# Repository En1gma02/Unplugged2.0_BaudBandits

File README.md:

BaudBandits

- kicad schematic
- kicad pcb
- cad model 
- 3d-cad (Contains screenshots of CAD)
- pcb (Contains screenshots of PCB)

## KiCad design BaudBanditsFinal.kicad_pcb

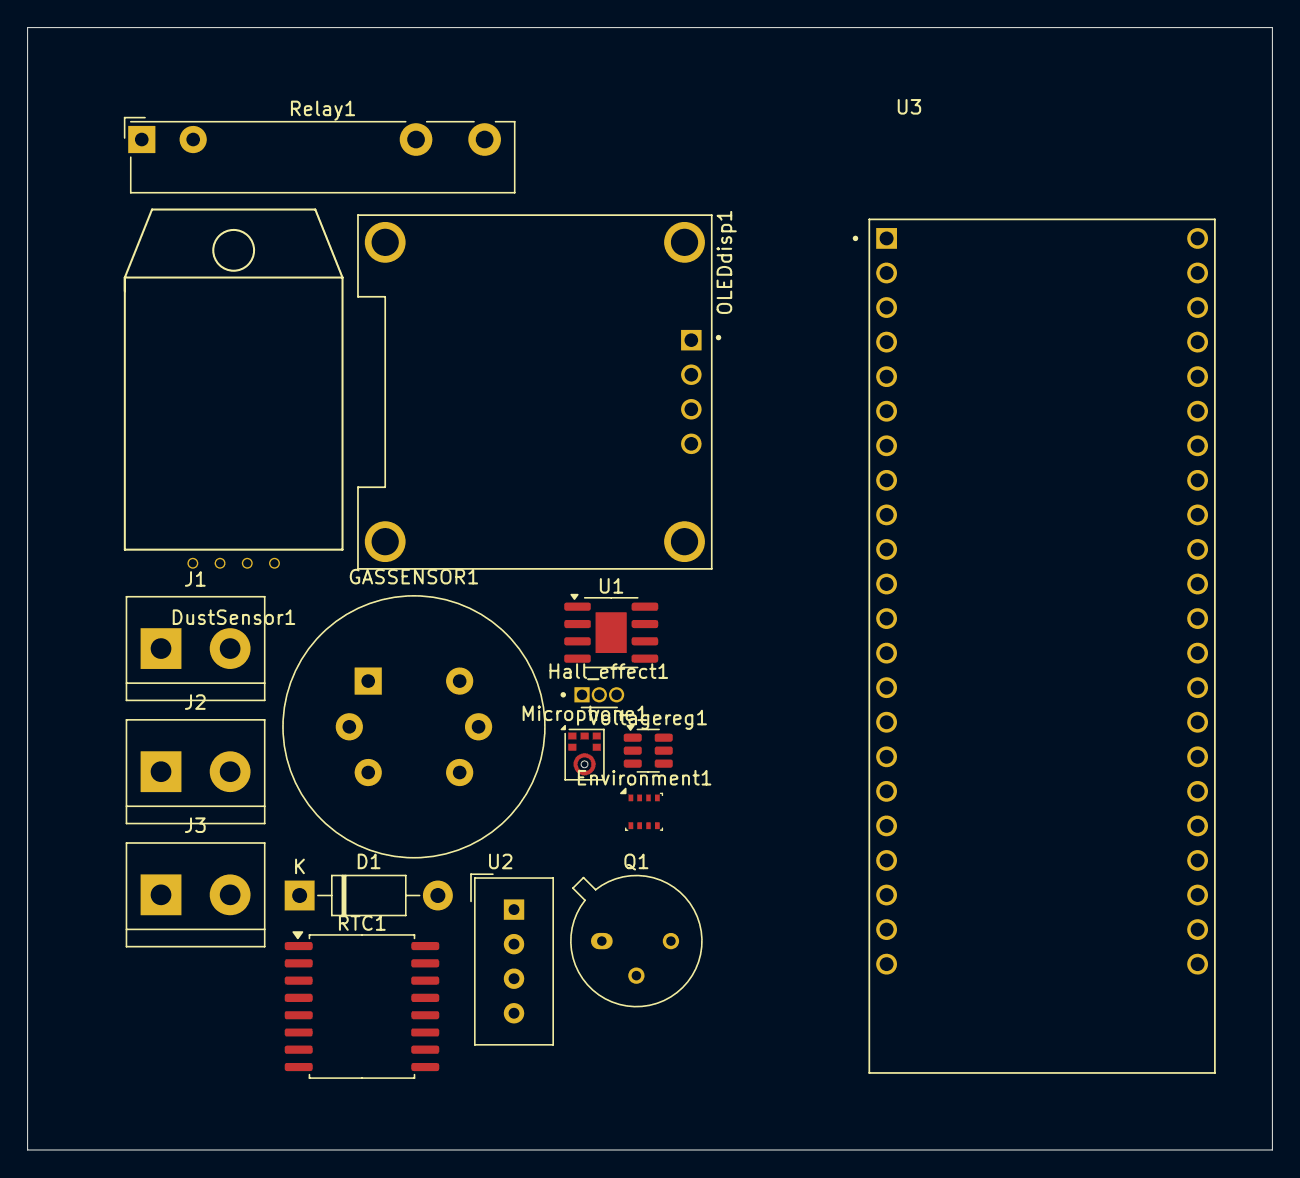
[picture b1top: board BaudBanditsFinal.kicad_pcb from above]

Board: 2 copper layers, 91.5 x 82.5 mm, 17 parts (0 on the bottom side), 19 nets, no tracks yet.

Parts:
D1: 1N5819; D_DO-41_SOD81_P10.16mm_Horizontal
DustSensor1: DHT22
Environment1: BME280; Bosch_LGA-8_2.5x2.5mm_P0.65mm_ClockwisePinNumbering
GASSENSOR1: MQ-6
Hall_effect1: MLX90217LUA-CAA-000-BU; TO92127P410H430-3
J1, J2, J3: Screw_Terminal_01x02; TerminalBlock_bornier-2_P5.08mm
Microphone1: ICS-43434; InvenSense_ICS-43434-6_3.5x2.65mm
OLEDdisp1: DM-OLED096-636; MODULE_DM-OLED096-636
Q1: 2N2219; TO-39-3
RTC1: DS3231M; SOIC-16W_7.5x10.3mm_P1.27mm
Relay1: Fujitsu_FTR-LYAA005x; Relay_SPST-NO_Fujitsu_FTR-LYAA005x_FormA_Vertical
U1: TP4056; SOIC-8-1EP_3.9x4.9mm_P1.27mm_EP2.29x3mm
U2: DHT11; Aosong_DHT11_5.5x12.0_P2.54mm
U3: ESP32-S3-DEVKITC-1-N8R2; XCVR_ESP32-S3-DEVKITC-1-N8R2
Voltagereg1: MT3608; SOT-23-6

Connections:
+5V: GASSENSOR1.2 (VH+), GASSENSOR1.4 (A2), Relay1.A2
/3V3: DustSensor1.1 (VCC), Environment1.2 (CSB), Environment1.8 (VDD), Hall_effect1.1 (VDD), Microphone1.5 (VDD), OLEDdisp1.2 (VCC_IN), RTC1.2 (VCC), U2.1 (VDD), U3.J1_1 (3V3), U3.J1_2 (3V3), Voltagereg1.3 (FB)
/GND: DustSensor1.4 (GND), Environment1.1 (GND), Environment1.5 (SDO), Environment1.7 (GND), GASSENSOR1.3 (B2), GASSENSOR1.5 (VH-), Hall_effect1.2 (GND), Microphone1.3 (GND), OLEDdisp1.1 (GND), Q1.1 (E), RTC1.5 (GND), RTC1.6 (GND), RTC1.7 (GND), RTC1.8 (GND), RTC1.9 (GND), RTC1.10 (GND), RTC1.11 (GND), RTC1.12 (GND), RTC1.13 (GND), U2.4 (GND), U3.J1_22 (GND), U3.J3_1 (GND), U3.J3_21 (GND), U3.J3_22 (GND), Voltagereg1.2 (GND)
/GPIO0: GASSENSOR1.1 (B1), U3.J3_14 (GPIO0)
/GPIO1: DustSensor1.2 (DATA), GASSENSOR1.6 (A1), U3.J3_4 (GPIO1)
/GPIO3: U2.2 (DATA), U3.J1_13 (GPIO3)
/GPIO15: Microphone1.6 (SD), U3.J1_8 (GPIO15)
/GPIO16: Microphone1.4 (SCK), U3.J1_9 (GPIO16)
/GPIO17: Microphone1.1 (WS), Microphone1.2 (LR), U3.J1_10 (GPIO17)
/GPIO18: Environment1.4 (SCK), U3.J1_11 (GPIO18)
/USB_D-/GPIO19: Environment1.3 (SDI), U3.J3_20 (USB_D-/GPIO19)
unnamed: J2.2, U1.3 (GND)
unnamed: D1.2 (A), J1.2
unnamed: D1.1 (K), U1.4 (VCC)
unnamed: J3.2, U1.5 (BAT), Voltagereg1.4 (EN), Voltagereg1.5 (IN)
unnamed: OLEDdisp1.3 (SCL), RTC1.16 (SCL), U3.J1_15 (GPIO9)
unnamed: OLEDdisp1.4 (SDA), RTC1.15 (SDA), U3.J1_12 (GPIO8)
unnamed: Q1.2 (B), U3.J3_19 (USB_D+/GPIO20)
unnamed: Q1.3 (C), Relay1.A1
